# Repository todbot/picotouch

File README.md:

# picotouch

Tiny capsense touch USB MIDI keyboard from a Raspberry Pi Pico

If you're looking for the synthesizer version,
that's at [github.com/todbot/picotouch_synth](https://github.com/todbot/picotouch_synth)

## Demos

https://user-images.githubusercontent.com/274093/216477797-90a1e4ca-b68f-4eb2-be46-de1d6d81551e.mp4

Also see videos in this Twitter thread : https://twitter.com/todbot/status/1382469033061093377

And check out [picotouch videos on my Youtube channel](https://www.youtube.com/@todbot/search?query=picotouch)

## Materials needed

If you [buy a black 'picotouch SMD' board from my Tindie store](https://www.tindie.com/products/todbot/picotouch-capsense-midi-keyboard-for-raspi-pico/), the <b>resistors are soldered</b> for you, so you only need to
[solder the Pico](https://www.youtube.com/watch?v=dW9LiOq3Dso).

If you're building one by hand, you will need:
- 1 - picotouch PCB ([order from OSHpark](https://oshpark.com/shared_projects/5MnI1jPf))
- 1 - Raspberry Pi Pico  **(NOTE: Not the Pico2, since its RP2350 chip has a hardware error)**
- 23 - 1M ohm 0805 SMD resistors  ([Digikey cart with this & Pico](https://www.digikey.com/short/w381rn4w))

## How to solder the Pico

It's not too bad!  A pretty easy first-time SMD soldering project.  Here's
[how to solder the Pico down](https://www.youtube.com/watch?v=dW9LiOq3Dso).
The technique is: line up the Pico solder one corner, solder the other, then finish all the rest.
In the video you see I don't get it aligned perfectly straight (hard to see around the camera), but it still works great!  ([Youtube version of the below video](https://www.youtube.com/watch?v=dW9LiOq3Dso))

https://user-images.githubusercontent.com/274093/217670870-b04d55ed-e37d-4be2-bea7-4985d2b3f8c4.mp4

## Firmware Installation

* Install CircuitPython
  - Hold down BOOT button while plugging in Pico to get RPI-RP2 drive
  - Download CircuitPython UF2 from https://circuitpython.org/board/raspberry_pi_pico/
  - Drag UF2 to RPI-RP2 drive. CircuitPython is now installed!

* Install CircuitPython libraries onto Pico
  - If you have Python on your computer you can do:
    ```
    pip3 install circup
    circup install adafruit_midi adafruit_debouncer adafruit_ticks
    ```
  - Otherwise, download the CircuitPython Libraries Bundle at https://circuitpython.org/libraries
    and copy over the `adafruit_midi`, `adafruit_debouncer`, & `adafruit_ticks` libraries
    to the `CIRCUITPY/lib` folder on the Pico.

* Install picotouch `code.py`
  - Via commandline:
    ```
    cp picotouch/circuitpython/picotouch/code.py /Volumes/CIRCUITPY/code.py
    ```
  - Or you can drag-n-drop using your computer's GUI
  - Note: this will delete the previous `code.py` on your Pico.
      Normally this is fine, but if it's not, be sure to save it if you want to keep it!

## Going further

There's other things you can do with the picotouch board.

- Use it as a MIDI slider bank

    Install
   [`picotouch_midislider/code.py`](https://github.com/todbot/picotouch/blob/main/circuitpython/picotouch_midislider/code.py) instead of the regular picotouch code.py.

   - youtube demo: [midislider demo video](https://youtu.be/1Psw3PLqYS8)

- Use it as a HID keyboard macropad

   - example code: [`picotouch_macropad/code.py`](https://github.com/todbot/picotouch/blob/main/circuitpython/picotouch_macropad/code.py)

   It's early days, but it's a start at that idea

## Press

- https://www.hackster.io/news/tod-kurt-s-ultra-slim-picotouch-is-a-button-free-23-key-raspberry-pi-pico-powered-midi-keyboard-700a3ce2227b (26 Feb 2023)
- https://www.raspberrypi.com/news/picotouch-synthesiser-magpimonday/ (22 Nov 2023)

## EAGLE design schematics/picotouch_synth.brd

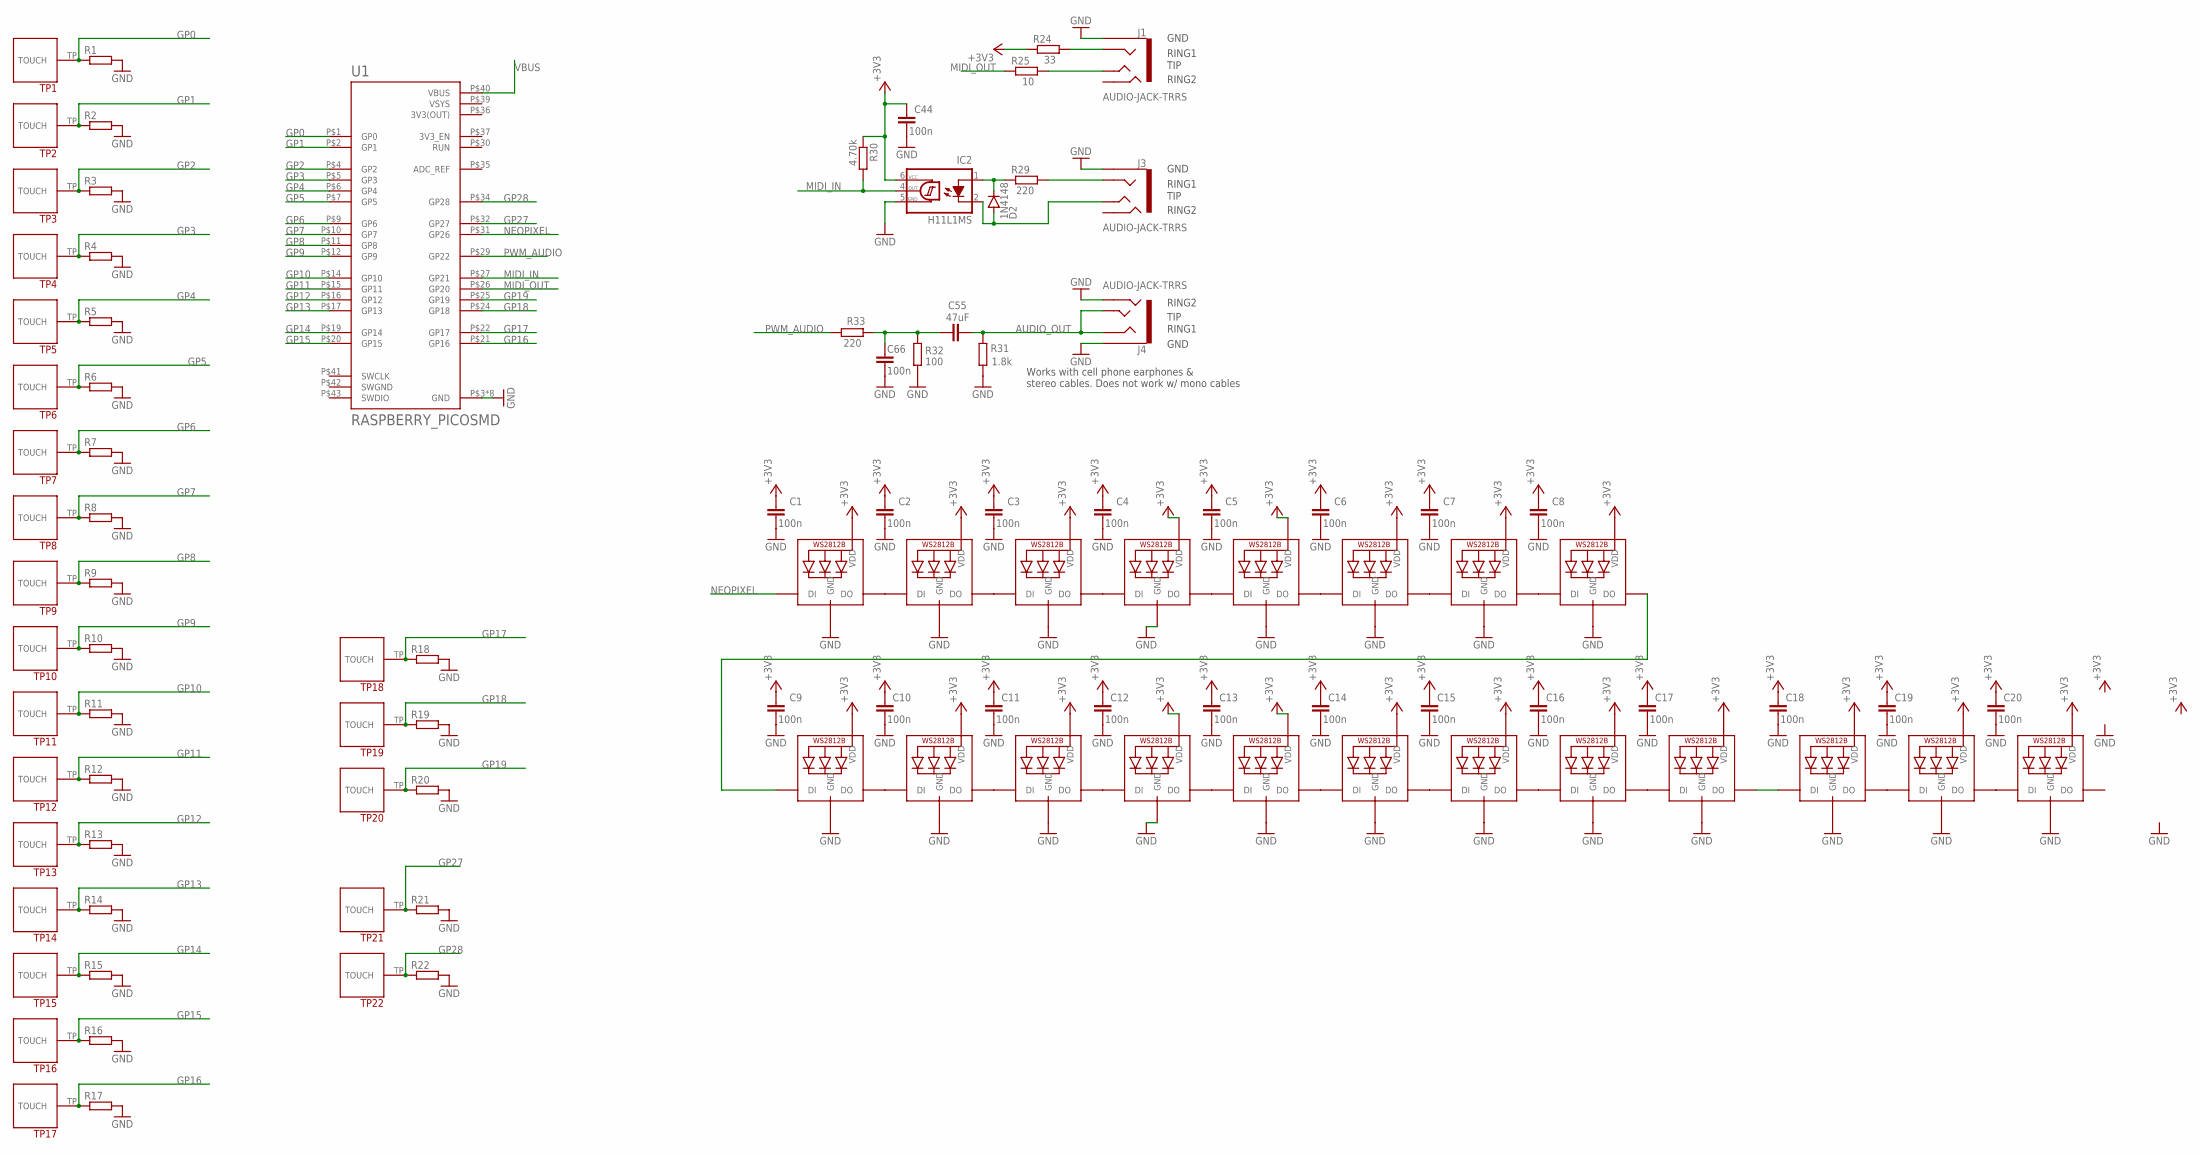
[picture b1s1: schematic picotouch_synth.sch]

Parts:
C1, C2, C3, C4, C5, C6, C7, C8, C9, C10, C11, C12, C13, C14, C15, C16, C17, C18, C19, C20, C44, C66: 100n; C0603
C55: 47uF; C0603
D2: 1N4148; SOD123
IC2: H11L1MS; DIL6-SMD; MPN2 H11L1S; LCSC C78589
J1, J3: AUDIO-JACK-TRRS; PJ-320D_SPARKFUN
J4: AUDIO-JACK-TRRS; PJ-320D_SPARKFUN; LCSC C431535
LED1, LED2, LED3, LED4, LED5, LED6, LED7, LED8, LED9, LED10, LED11, LED12, LED13, LED14, LED15, LED16, LED17, LED18, LED19, LED20: WS2812B3535; LED3535
R1, R2, R3, R4, R5, R6, R7, R8, R9, R10, R11, R12, R13, R14, R15, R16, R17: R-EU_R0805; R0805
R18, R19, R20, R21, R22: R-EU_R0603; R0603
R24: 33; R0603
R25: 10; R0603
R29, R33: 220; R0603
R30: 4.70k; R0603
R31: 1.8k; R0603
R32: 100; R0603
TP1, TP2, TP3, TP4, TP5, TP6, TP7, TP8, TP9, TP10, TP11, TP12, TP13, TP14, TP15, TP16, TP17: TOUCHPADA
TP18, TP19, TP20, TP21, TP22: TOUCHPADB
U1: RASPBERRY_PICOSMD; PICO-PKG-SMD

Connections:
3V3(OUT): U1.P$36 (3V3(OUT))
+3V3: C1.1, C2.1, C3.1, C4.1, C5.1, C6.1, C7.1, C8.1, C9.1, C10.1, C11.1, C12.1, C13.1, C14.1, C15.1, C16.1, C17.1, C18.1, C19.1, C20.1, C44.1, IC2.6 (VCC), LED1.2 (VDD), LED2.2 (VDD), LED3.2 (VDD), LED4.2 (VDD), LED5.2 (VDD), LED6.2 (VDD), LED7.2 (VDD), LED8.2 (VDD), LED9.2 (VDD), LED10.2 (VDD), LED11.2 (VDD), LED12.2 (VDD), LED13.2 (VDD), LED14.2 (VDD), LED15.2 (VDD), LED16.2 (VDD), LED17.2 (VDD), LED18.2 (VDD), LED19.2 (VDD), LED20.2 (VDD), R24.1, R30.1
AUDIO_OUT: C55.2, J4.RING1, J4.TIP, R31.1
GND: C1.2, C2.2, C3.2, C4.2, C5.2, C6.2, C7.2, C8.2, C9.2, C10.2, C11.2, C12.2, C13.2, C14.2, C15.2, C16.2, C17.2, C18.2, C19.2, C20.2, C44.2, C66.2, IC2.5 (GND), J1.EARTH, J3.EARTH, J4.EARTH, J4.RING2, LED1.4 (GND), LED2.4 (GND), LED3.4 (GND), LED4.4 (GND), LED5.4 (GND), LED6.4 (GND), LED7.4 (GND), LED8.4 (GND), LED9.4 (GND), LED10.4 (GND), LED11.4 (GND), LED12.4 (GND), LED13.4 (GND), LED14.4 (GND), LED15.4 (GND), LED16.4 (GND), LED17.4 (GND), LED18.4 (GND), LED19.4 (GND), LED20.4 (GND), R1.2, R2.2, R3.2, R4.2, R5.2, R6.2, R7.2, R8.2, R9.2, R10.2, R11.2, R12.2, R13.2, R14.2, R15.2, R16.2, R17.2, R18.2, R19.2, R20.2, R21.2, R22.2, R31.2, R32.1, U1.P$3 (GND), U1.P$8 (GND), U1.P$13 (GND), U1.P$18 (GND), U1.P$23 (GND), U1.P$28 (GND), U1.P$33 (GND), U1.P$38 (GND)
GP0: R1.1, TP1.TP, U1.P$1 (GP0)
GP1: R2.1, TP2.TP, U1.P$2 (GP1)
GP2: R3.1, TP3.TP, U1.P$4 (GP2)
GP3: R4.1, TP4.TP, U1.P$5 (GP3)
GP4: R5.1, TP5.TP, U1.P$6 (GP4)
GP5: R6.1, TP6.TP, U1.P$7 (GP5)
GP6: R7.1, TP7.TP, U1.P$9 (GP6)
GP7: R8.1, TP8.TP, U1.P$10 (GP7)
GP8: R9.1, TP9.TP, U1.P$11 (GP8)
GP9: R10.1, TP10.TP, U1.P$12 (GP9)
GP10: R11.1, TP11.TP, U1.P$14 (GP10)
GP11: R12.1, TP12.TP, U1.P$15 (GP11)
GP12: R13.1, TP13.TP, U1.P$16 (GP12)
GP13: R14.1, TP14.TP, U1.P$17 (GP13)
GP14: R15.1, TP15.TP, U1.P$19 (GP14)
GP15: R16.1, TP16.TP, U1.P$20 (GP15)
GP16: R17.1, TP17.TP, U1.P$21 (GP16)
GP17: R18.1, TP18.TP, U1.P$22 (GP17)
GP18: R19.1, TP19.TP, U1.P$24 (GP18)
GP19: R20.1, TP20.TP, U1.P$25 (GP19)
GP27: R21.1, TP21.TP, U1.P$32 (GP27)
GP28: R22.1, TP22.TP, U1.P$34 (GP28)
MIDI_IN: IC2.4 (OUT), R30.2, U1.P$27 (GP21)
MIDI_OUT: R25.1, U1.P$26 (GP20)
unnamed: D2.C, IC2.1 (A), R29.1
unnamed: J1.TIP, R25.2
unnamed: D2.A, IC2.2 (C), J3.TIP
unnamed: J3.RING1, R29.2
unnamed: C55.1, C66.1, R32.2, R33.1
unnamed: J1.RING1, R24.2
unnamed: LED1.3 (DO), LED2.1 (DI)
unnamed: LED4.3 (DO), LED5.1 (DI)
unnamed: LED5.3 (DO), LED6.1 (DI)
unnamed: LED6.3 (DO), LED7.1 (DI)
unnamed: LED7.3 (DO), LED8.1 (DI)
unnamed: LED2.3 (DO), LED3.1 (DI)
unnamed: LED3.3 (DO), LED4.1 (DI)
unnamed: LED9.3 (DO), LED10.1 (DI)
unnamed: LED12.3 (DO), LED13.1 (DI)
unnamed: LED13.3 (DO), LED14.1 (DI)
unnamed: LED14.3 (DO), LED15.1 (DI)
unnamed: LED15.3 (DO), LED16.1 (DI)
unnamed: LED10.3 (DO), LED11.1 (DI)
unnamed: LED11.3 (DO), LED12.1 (DI)
unnamed: LED8.3 (DO), LED9.1 (DI)
unnamed: LED16.3 (DO), LED17.1 (DI)
unnamed: LED18.3 (DO), LED19.1 (DI)
unnamed: LED19.3 (DO), LED20.1 (DI)
unnamed: LED17.3 (DO), LED18.1 (DI)
NEOPIXEL: LED1.1 (DI), U1.P$31 (GP26)
PWM_AUDIO: R33.2, U1.P$29 (GP22)
SWGND: U1.P$42 (SWGND)
VBUS: U1.P$40 (VBUS)
VSYS: U1.P$39 (VSYS)

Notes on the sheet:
RING2
RING1
GND
TIP
Works with cell phone earphones & stereo cables. Does not work w/ mono cables

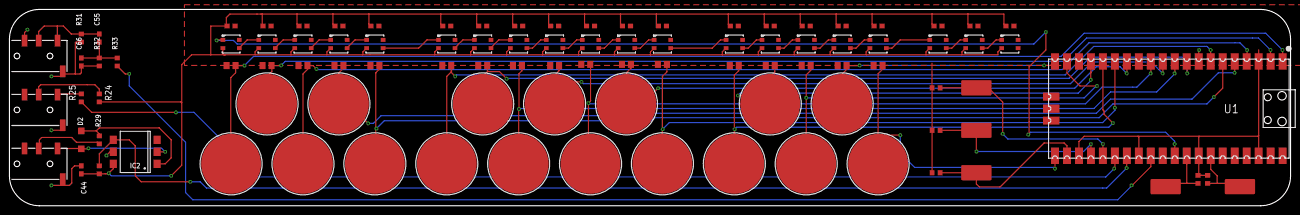
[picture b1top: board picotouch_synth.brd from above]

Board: 2 copper layers, 271.6 x 41.6 mm, 100 parts (0 on the bottom side), 54 nets.

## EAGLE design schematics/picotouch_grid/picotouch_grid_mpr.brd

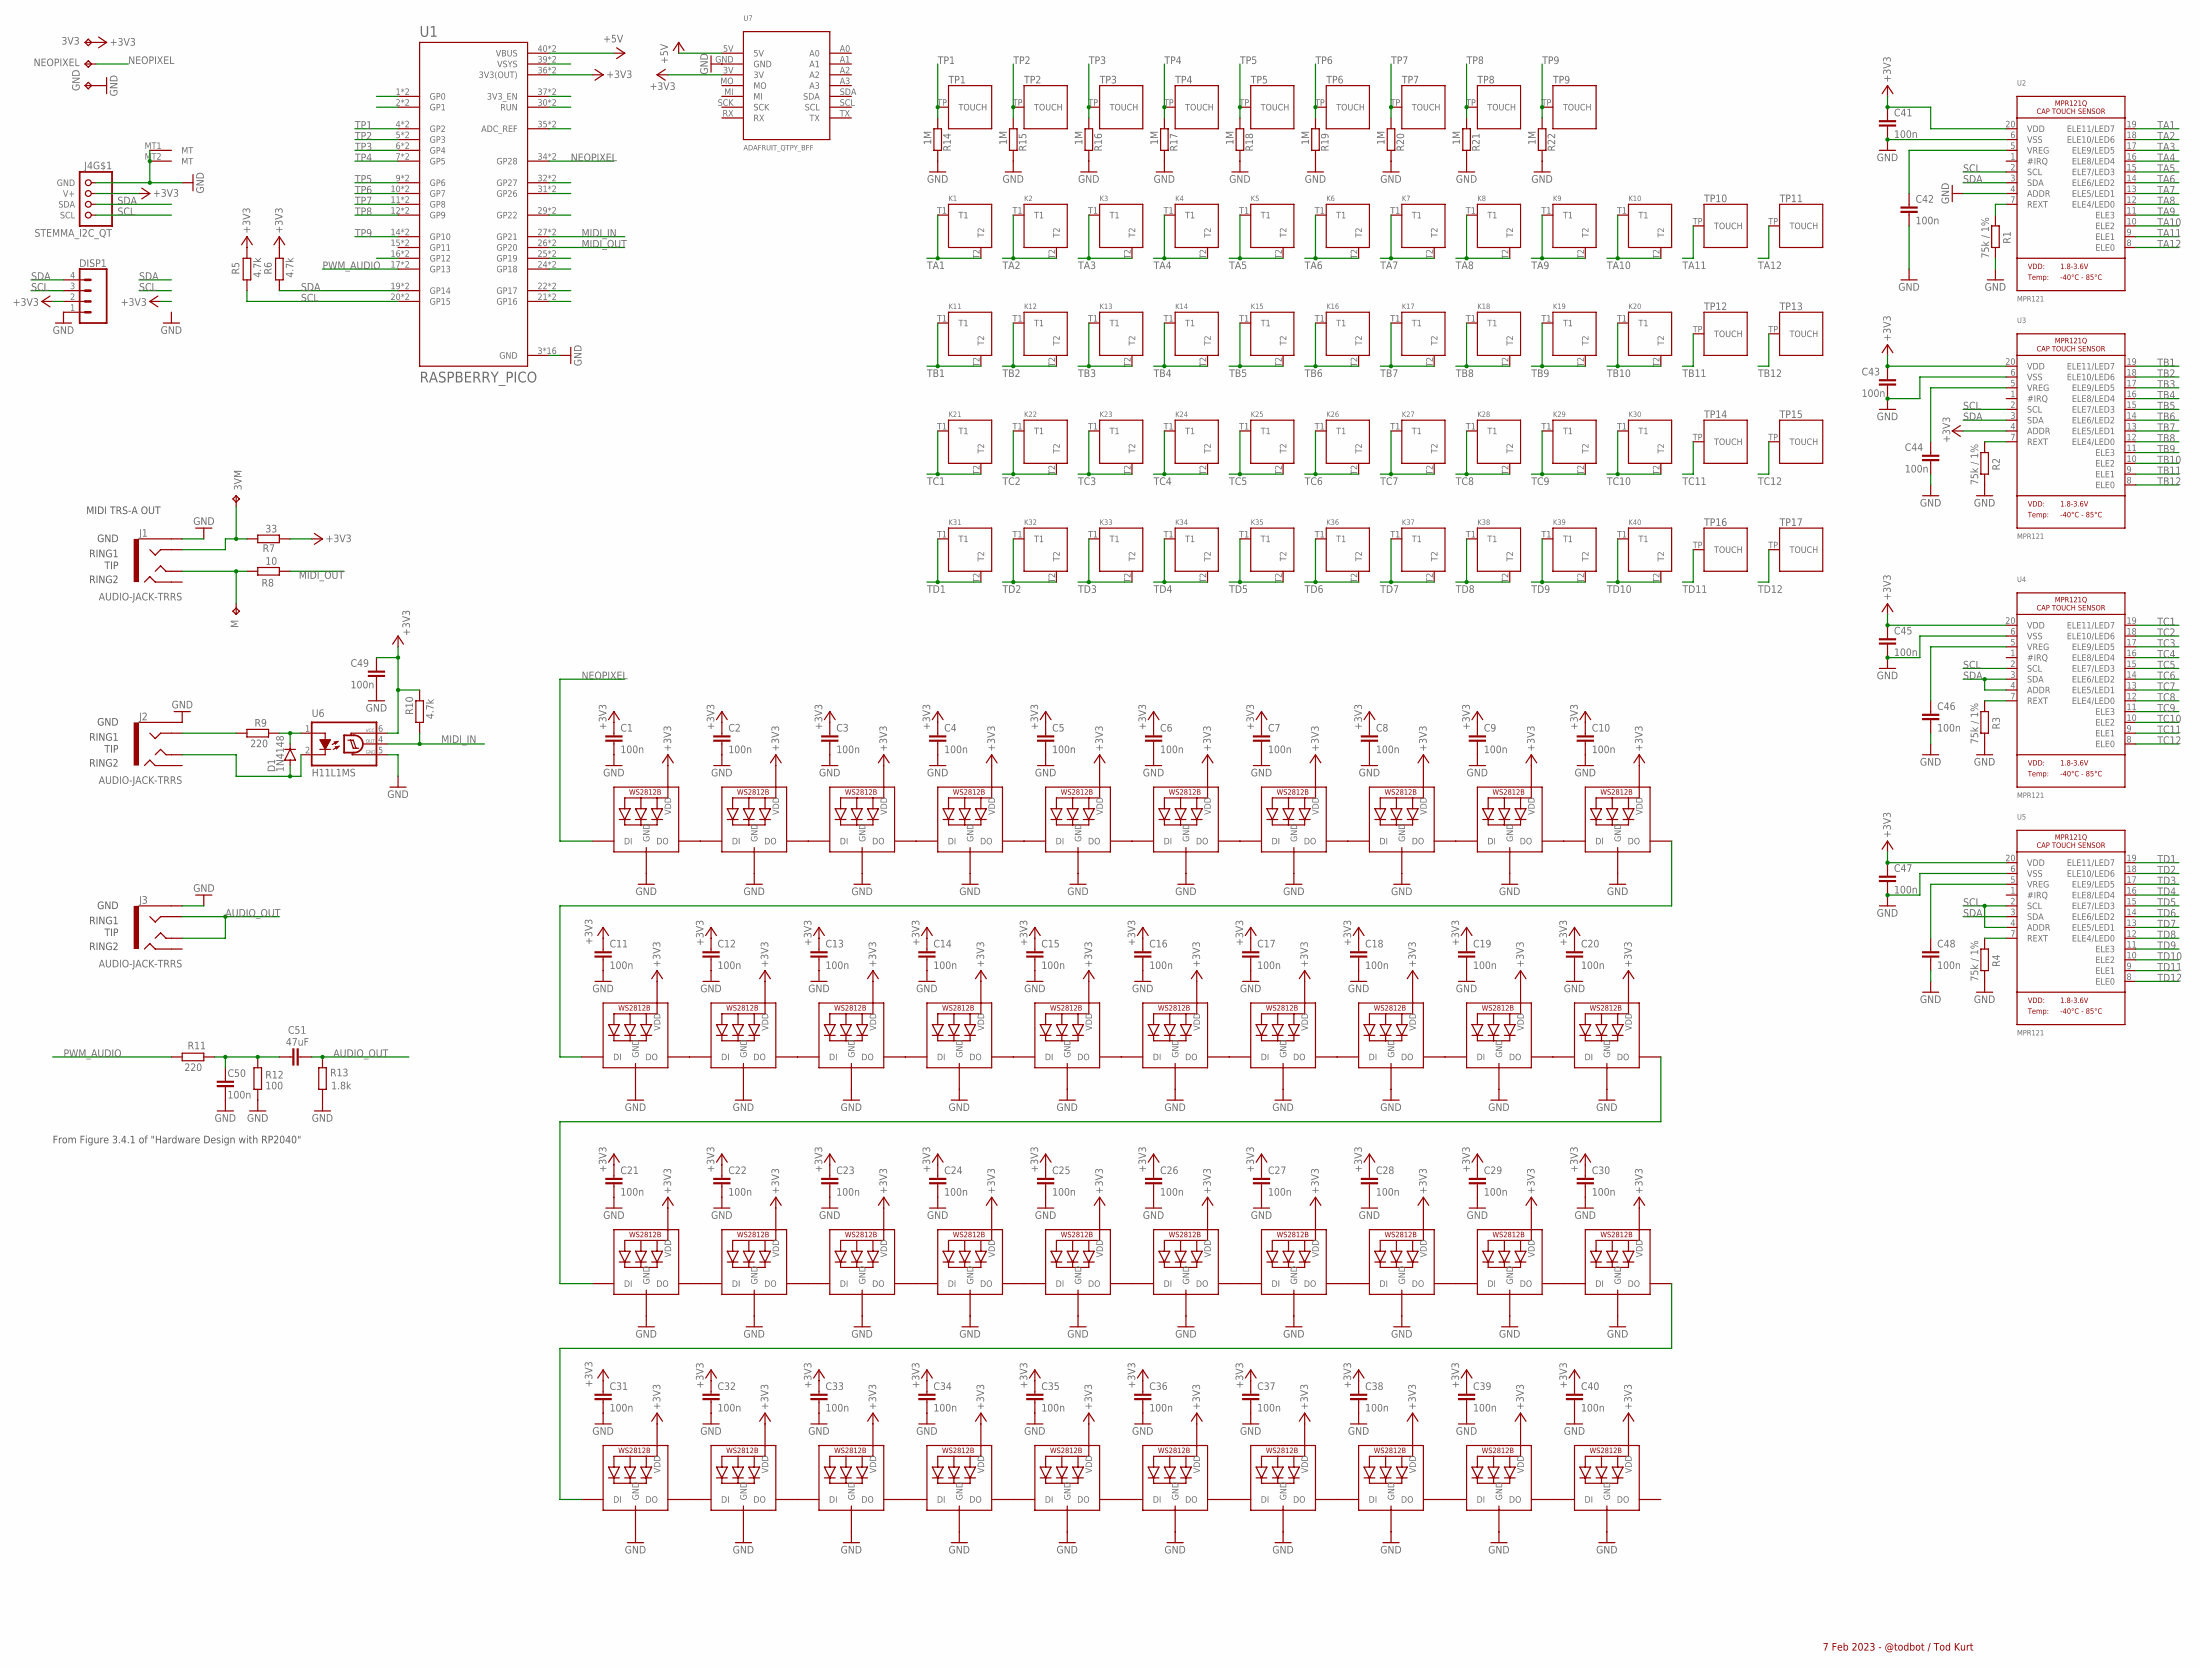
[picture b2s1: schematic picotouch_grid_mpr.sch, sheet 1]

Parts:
3V3, 3VM: TPTP15R; TP15R
C1, C2, C3, C4, C5, C6, C7, C8, C9, C10, C11, C12, C13, C14, C15, C16, C17, C18, C19, C20, C21, C22, C23, C24, C25, C26, C27, C28, C29, C30, C31, C32, C33, C34, C35, C36, C37, C38, C39, C40, C41, C42, C43, C44, C45, C46, C47, C48, C49, C50: 100n; C0603
C51: 47uF; C0805
D1: 1N4148; SOD123
DISP1: CONN_04; 1X04
GND: TPTP15R; TP15R
J1, J3: AUDIO-JACK-TRRS; PJ-320D_SPARKFUN; LCSC C431535
J2: AUDIO-JACK-TRRS; PJ-320D_SPARKFUN
J4: STEMMA_I2C_QT; JST_SH4; MPN HC-1.0-4PWT; LCSC2 C160404
K1, K2, K3, K4, K5, K6, K7, K8, K9, K10, K11, K12, K13, K14, K15, K16, K17, K18, K19, K20, K21, K22, K23, K24, K25, K26, K27, K28, K29, K30, K31, K32, K33, K34, K35, K36, K37, K38, K39, K40: TOUCHKEYH; TOUCHPAD_KEY_0.5IN_LEDHOLE
LED1: MICROBUILDER_WS2812B_SK6812E; MICROBUILDER_NEO3535_REVERSE; LCSC C5149201
LED2, LED3, LED4, LED5, LED6, LED7, LED8, LED9, LED10, LED11, LED12, LED13, LED14, LED15, LED16, LED17, LED18, LED19, LED20, LED21, LED22, LED23, LED24, LED25, LED26, LED27, LED28, LED29, LED30, LED31, LED32, LED33, LED34, LED35, LED36, LED37, LED38, LED39, LED40: MICROBUILDER_WS2812B_SK6812E; MICROBUILDER_NEO3535_REVERSE
M: TPTP15R; TP15R
NEOPIXEL: TPTP15R; TP15R
R1, R2, R3, R4: 75k / 1%; R0603
R5, R6, R10: 4.7k; R0603
R7: 33; R0603
R8: 10; R0603
R9, R11: 220; R0603
R12: 100; R0603
R13: 1.8k; R0603
R14, R15, R16, R17, R18, R19, R20, R21, R22: 1M; R0603
TP1, TP2, TP3, TP4, TP5, TP6, TP7, TP8, TP9, TP10, TP11, TP12, TP13, TP14, TP15, TP16, TP17: TOUCHPADB
U1: RASPBERRY_PICO; PICO-PKG-DUALSMD
U2, U3, U4, U5: MPR121; QFN20_3MM_NOTHERMAL; LCSC C91322
U6: H11L1MS; DIL6-SMD; MPN2 H11L1S; LCSC C78589
U7: ADAFRUIT_QTPY_BFF; ADAFRUIT_QTPY_BFF_LIPO

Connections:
+3V3: 3V3.TP, C1.1, C2.1, C3.1, C4.1, C5.1, C6.1, C7.1, C8.1, C9.1, C10.1, C11.1, C12.1, C13.1, C14.1, C15.1, C16.1, C17.1, C18.1, C19.1, C20.1, C21.1, C22.1, C23.1, C24.1, C25.1, C26.1, C27.1, C28.1, C29.1, C30.1, C31.1, C32.1, C33.1, C34.1, C35.1, C36.1, C37.1, C38.1, C39.1, C40.1, C41.1, C43.1, C45.1, C47.1, C49.1, DISP1.2, J4.2 (V+), LED1.1-VDD (VDD), LED2.1-VDD (VDD), LED3.1-VDD (VDD), LED4.1-VDD (VDD), LED5.1-VDD (VDD), LED6.1-VDD (VDD), LED7.1-VDD (VDD), LED8.1-VDD (VDD), LED9.1-VDD (VDD), LED10.1-VDD (VDD), LED11.1-VDD (VDD), LED12.1-VDD (VDD), LED13.1-VDD (VDD), LED14.1-VDD (VDD), LED15.1-VDD (VDD), LED16.1-VDD (VDD), LED17.1-VDD (VDD), LED18.1-VDD (VDD), LED19.1-VDD (VDD), LED20.1-VDD (VDD), LED21.1-VDD (VDD), LED22.1-VDD (VDD), LED23.1-VDD (VDD), LED24.1-VDD (VDD), LED25.1-VDD (VDD), LED26.1-VDD (VDD), LED27.1-VDD (VDD), LED28.1-VDD (VDD), LED29.1-VDD (VDD), LED30.1-VDD (VDD), LED31.1-VDD (VDD), LED32.1-VDD (VDD), LED33.1-VDD (VDD), LED34.1-VDD (VDD), LED35.1-VDD (VDD), LED36.1-VDD (VDD), LED37.1-VDD (VDD), LED38.1-VDD (VDD), LED39.1-VDD (VDD), LED40.1-VDD (VDD), R5.1, R6.1, R7.2, R10.1, U1.36 (3V3(OUT)), U1.36' (3V3(OUT)), U2.20 (VDD), U3.4 (ADDR), U3.20 (VDD), U4.20 (VDD), U5.20 (VDD), U6.6 (VCC), U7.3V
+5V: U1.40 (VBUS), U1.40' (VBUS), U7.5V
AUDIO_OUT: C51.2, J3.RING1, J3.TIP, R13.1
GND: C1.2, C2.2, C3.2, C4.2, C5.2, C6.2, C7.2, C8.2, C9.2, C10.2, C11.2, C12.2, C13.2, C14.2, C15.2, C16.2, C17.2, C18.2, C19.2, C20.2, C21.2, C22.2, C23.2, C24.2, C25.2, C26.2, C27.2, C28.2, C29.2, C30.2, C31.2, C32.2, C33.2, C34.2, C35.2, C36.2, C37.2, C38.2, C39.2, C40.2, C41.2, C42.2, C43.2, C44.2, C45.2, C46.2, C47.2, C48.2, C49.2, C50.2, DISP1.1, GND.TP, J1.EARTH, J2.EARTH, J3.EARTH, J4.1 (GND), J4.MT1 (MT), J4.MT2 (MT), LED1.3-GND (GND), LED2.3-GND (GND), LED3.3-GND (GND), LED4.3-GND (GND), LED5.3-GND (GND), LED6.3-GND (GND), LED7.3-GND (GND), LED8.3-GND (GND), LED9.3-GND (GND), LED10.3-GND (GND), LED11.3-GND (GND), LED12.3-GND (GND), LED13.3-GND (GND), LED14.3-GND (GND), LED15.3-GND (GND), LED16.3-GND (GND), LED17.3-GND (GND), LED18.3-GND (GND), LED19.3-GND (GND), LED20.3-GND (GND), LED21.3-GND (GND), LED22.3-GND (GND), LED23.3-GND (GND), LED24.3-GND (GND), LED25.3-GND (GND), LED26.3-GND (GND), LED27.3-GND (GND), LED28.3-GND (GND), LED29.3-GND (GND), LED30.3-GND (GND), LED31.3-GND (GND), LED32.3-GND (GND), LED33.3-GND (GND), LED34.3-GND (GND), LED35.3-GND (GND), LED36.3-GND (GND), LED37.3-GND (GND), LED38.3-GND (GND), LED39.3-GND (GND), LED40.3-GND (GND), R1.1, R2.1, R3.1, R4.1, R12.1, R13.2, R14.1, R15.1, R16.1, R17.1, R18.1, R19.1, R20.1, R21.1, R22.1, U1.3 (GND), U1.3' (GND), U1.8 (GND), U1.8' (GND), U1.13 (GND), U1.13' (GND), U1.18 (GND), U1.18' (GND), U1.23 (GND), U1.23' (GND), U1.28 (GND), U1.28' (GND), U1.33 (GND), U1.33' (GND), U1.38 (GND), U1.38' (GND), U2.4 (ADDR), U2.6 (VSS), U3.6 (VSS), U4.6 (VSS), U5.6 (VSS), U6.5 (GND), U7.GND
MIDI_IN: R10.2, U1.27 (GP21), U1.27' (GP21), U6.4 (OUT)
MIDI_OUT: R8.2, U1.26 (GP20), U1.26' (GP20)
unnamed: LED1.2-DOUT (DO), LED2.4-DIN (DI)
unnamed: LED2.2-DOUT (DO), LED3.4-DIN (DI)
unnamed: LED4.2-DOUT (DO), LED5.4-DIN (DI)
unnamed: LED5.2-DOUT (DO), LED6.4-DIN (DI)
unnamed: LED3.2-DOUT (DO), LED4.4-DIN (DI)
unnamed: LED7.2-DOUT (DO), LED8.4-DIN (DI)
unnamed: LED8.2-DOUT (DO), LED9.4-DIN (DI)
unnamed: J1.TIP, M.TP, R8.1
unnamed: LED11.2-DOUT (DO), LED12.4-DIN (DI)
unnamed: LED9.2-DOUT (DO), LED10.4-DIN (DI)
unnamed: LED6.2-DOUT (DO), LED7.4-DIN (DI)
unnamed: LED14.2-DOUT (DO), LED15.4-DIN (DI)
unnamed: LED15.2-DOUT (DO), LED16.4-DIN (DI)
unnamed: LED13.2-DOUT (DO), LED14.4-DIN (DI)
unnamed: LED17.2-DOUT (DO), LED18.4-DIN (DI)
unnamed: LED18.2-DOUT (DO), LED19.4-DIN (DI)
unnamed: LED19.2-DOUT (DO), LED20.4-DIN (DI)
unnamed: LED16.2-DOUT (DO), LED17.4-DIN (DI)
unnamed: LED12.2-DOUT (DO), LED13.4-DIN (DI)
unnamed: LED21.2-DOUT (DO), LED22.4-DIN (DI)
unnamed: LED22.2-DOUT (DO), LED23.4-DIN (DI)
unnamed: LED24.2-DOUT (DO), LED25.4-DIN (DI)
unnamed: LED25.2-DOUT (DO), LED26.4-DIN (DI)
unnamed: LED23.2-DOUT (DO), LED24.4-DIN (DI)
unnamed: LED27.2-DOUT (DO), LED28.4-DIN (DI)
unnamed: LED28.2-DOUT (DO), LED29.4-DIN (DI)
unnamed: LED31.2-DOUT (DO), LED32.4-DIN (DI)
unnamed: LED29.2-DOUT (DO), LED30.4-DIN (DI)
unnamed: LED26.2-DOUT (DO), LED27.4-DIN (DI)
unnamed: LED34.2-DOUT (DO), LED35.4-DIN (DI)
unnamed: LED35.2-DOUT (DO), LED36.4-DIN (DI)
unnamed: LED33.2-DOUT (DO), LED34.4-DIN (DI)
unnamed: LED37.2-DOUT (DO), LED38.4-DIN (DI)
unnamed: LED38.2-DOUT (DO), LED39.4-DIN (DI)
unnamed: LED39.2-DOUT (DO), LED40.4-DIN (DI)
unnamed: LED36.2-DOUT (DO), LED37.4-DIN (DI)
unnamed: LED32.2-DOUT (DO), LED33.4-DIN (DI)
unnamed: 3VM.TP, J1.RING1, R7.1
unnamed: U1.21 (GP16), U1.21' (GP16)
unnamed: U1.22 (GP17), U1.22' (GP17)
unnamed: U1.24 (GP18), U1.24' (GP18)
unnamed: U1.25 (GP19), U1.25' (GP19)
unnamed: R2.2, U3.7 (REXT)
unnamed: C44.1, U3.5 (VREG)
unnamed: U1.32 (GP27), U1.32' (GP27)
unnamed: D1.C, R9.1, U6.1 (A)
unnamed: D1.A, J2.TIP, U6.2 (C)
unnamed: J2.RING1, R9.2
unnamed: R4.2, U5.7 (REXT)
unnamed: C48.1, U5.5 (VREG)
unnamed: U1.31 (GP26), U1.31' (GP26)
unnamed: U1.29 (GP22), U1.29' (GP22)
unnamed: U1.35 (ADC_REF), U1.35' (ADC_REF)
unnamed: U1.30 (RUN), U1.30' (RUN)
unnamed: C50.1, C51.1, R11.1, R12.2
unnamed: U1.37 (3V3_EN), U1.37' (3V3_EN)
unnamed: U1.2 (GP1), U1.2' (GP1)
unnamed: R3.2, U4.7 (REXT)
unnamed: C46.1, U4.5 (VREG)
unnamed: U1.1 (GP0), U1.1' (GP0)
unnamed: U1.39 (VSYS), U1.39' (VSYS)
unnamed: U1.16 (GP12), U1.16' (GP12)
unnamed: C42.1, U2.5 (VREG)
unnamed: R1.2, U2.7 (REXT)
NEOPIXEL: LED1.4-DIN (DI), NEOPIXEL.TP, U1.34 (GP28), U1.34' (GP28)
NEOPIXEL0: LED10.2-DOUT (DO), LED11.4-DIN (DI)
NEOPIXEL1: LED20.2-DOUT (DO), LED21.4-DIN (DI)
NEOPIXEL2: LED30.2-DOUT (DO), LED31.4-DIN (DI)
PWM_AUDIO: R11.2, U1.17 (GP13), U1.17' (GP13)
SCL: DISP1.3, J4.4 (SCL), R5.2, U1.20 (GP15), U1.20' (GP15), U2.2 (SCL), U3.2 (SCL), U4.2 (SCL), U5.2 (SCL), U5.4 (ADDR)
SDA: DISP1.4, J4.3 (SDA), R6.2, U1.19 (GP14), U1.19' (GP14), U2.3 (SDA), U3.3 (SDA), U4.3 (SDA), U4.4 (ADDR), U5.3 (SDA)
TA1: K1.T1, K1.T2, U2.19 (ELE11/LED7)
TA2: K2.T1, K2.T2, U2.18 (ELE10/LED6)
TA3: K3.T1, K3.T2, U2.17 (ELE9/LED5)
TA4: K4.T1, K4.T2, U2.16 (ELE8/LED4)
TA5: K5.T1, K5.T2, U2.15 (ELE7/LED3)
TA6: K6.T1, K6.T2, U2.14 (ELE6/LED2)
TA7: K7.T1, K7.T2, U2.13 (ELE5/LED1)
TA8: K8.T1, K8.T2, U2.12 (ELE4/LED0)
TA9: K9.T1, K9.T2, U2.11 (ELE3)
TA10: K10.T1, K10.T2, U2.10 (ELE2)
TA11: TP10.TP, U2.9 (ELE1)
TA12: TP11.TP, U2.8 (ELE0)
TB1: K11.T1, K11.T2, U3.19 (ELE11/LED7)
TB2: K12.T1, K12.T2, U3.18 (ELE10/LED6)
TB3: K13.T1, K13.T2, U3.17 (ELE9/LED5)
TB4: K14.T1, K14.T2, U3.16 (ELE8/LED4)
TB5: K15.T1, K15.T2, U3.15 (ELE7/LED3)
TB6: K16.T1, K16.T2, U3.14 (ELE6/LED2)
TB7: K17.T1, K17.T2, U3.13 (ELE5/LED1)
TB8: K18.T1, K18.T2, U3.12 (ELE4/LED0)
TB9: K19.T1, K19.T2, U3.11 (ELE3)
TB10: K20.T1, K20.T2, U3.10 (ELE2)
TB11: TP12.TP, U3.9 (ELE1)
TB12: TP13.TP, U3.8 (ELE0)
TC1: K21.T1, K21.T2, U4.19 (ELE11/LED7)
TC2: K22.T1, K22.T2, U4.18 (ELE10/LED6)
TC3: K23.T1, K23.T2, U4.17 (ELE9/LED5)
TC4: K24.T1, K24.T2, U4.16 (ELE8/LED4)
TC5: K25.T1, K25.T2, U4.15 (ELE7/LED3)
TC6: K26.T1, K26.T2, U4.14 (ELE6/LED2)
TC7: K27.T1, K27.T2, U4.13 (ELE5/LED1)
TC8: K28.T1, K28.T2, U4.12 (ELE4/LED0)
TC9: K29.T1, K29.T2, U4.11 (ELE3)
TC10: K30.T1, K30.T2, U4.10 (ELE2)
TC11: TP14.TP, U4.9 (ELE1)
TC12: TP15.TP, U4.8 (ELE0)
TD1: K31.T1, K31.T2, U5.19 (ELE11/LED7)
TD2: K32.T1, K32.T2, U5.18 (ELE10/LED6)
TD3: K33.T1, K33.T2, U5.17 (ELE9/LED5)
TD4: K34.T1, K34.T2, U5.16 (ELE8/LED4)
TD5: K35.T1, K35.T2, U5.15 (ELE7/LED3)
TD6: K36.T1, K36.T2, U5.14 (ELE6/LED2)
TD7: K37.T1, K37.T2, U5.13 (ELE5/LED1)
TD8: K38.T1, K38.T2, U5.12 (ELE4/LED0)
TD9: K39.T1, K39.T2, U5.11 (ELE3)
TD10: K40.T1, K40.T2, U5.10 (ELE2)
TD11: TP16.TP, U5.9 (ELE1)
TD12: TP17.TP, U5.8 (ELE0)
TP1: R14.2, TP1.TP, U1.4 (GP2), U1.4' (GP2)
TP2: R15.2, TP2.TP, U1.5 (GP3), U1.5' (GP3)
TP3: R16.2, TP3.TP, U1.6 (GP4), U1.6' (GP4)
TP4: R17.2, TP4.TP, U1.7 (GP5), U1.7' (GP5)
TP5: R18.2, TP5.TP, U1.9 (GP6), U1.9' (GP6)
TP6: R19.2, TP6.TP, U1.10 (GP7), U1.10' (GP7)
TP7: R20.2, TP7.TP, U1.11 (GP8), U1.11' (GP8)
TP8: R21.2, TP8.TP, U1.12 (GP9), U1.12' (GP9)
TP9: R22.2, TP9.TP, U1.14 (GP10), U1.14' (GP10)

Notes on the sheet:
MIDI TRS-A OUT
RING2
RING1
GND
TIP
7 Feb 2023 - @todbot / Tod Kurt
From Figure 3.4.1 of "Hardware Design with RP2040"

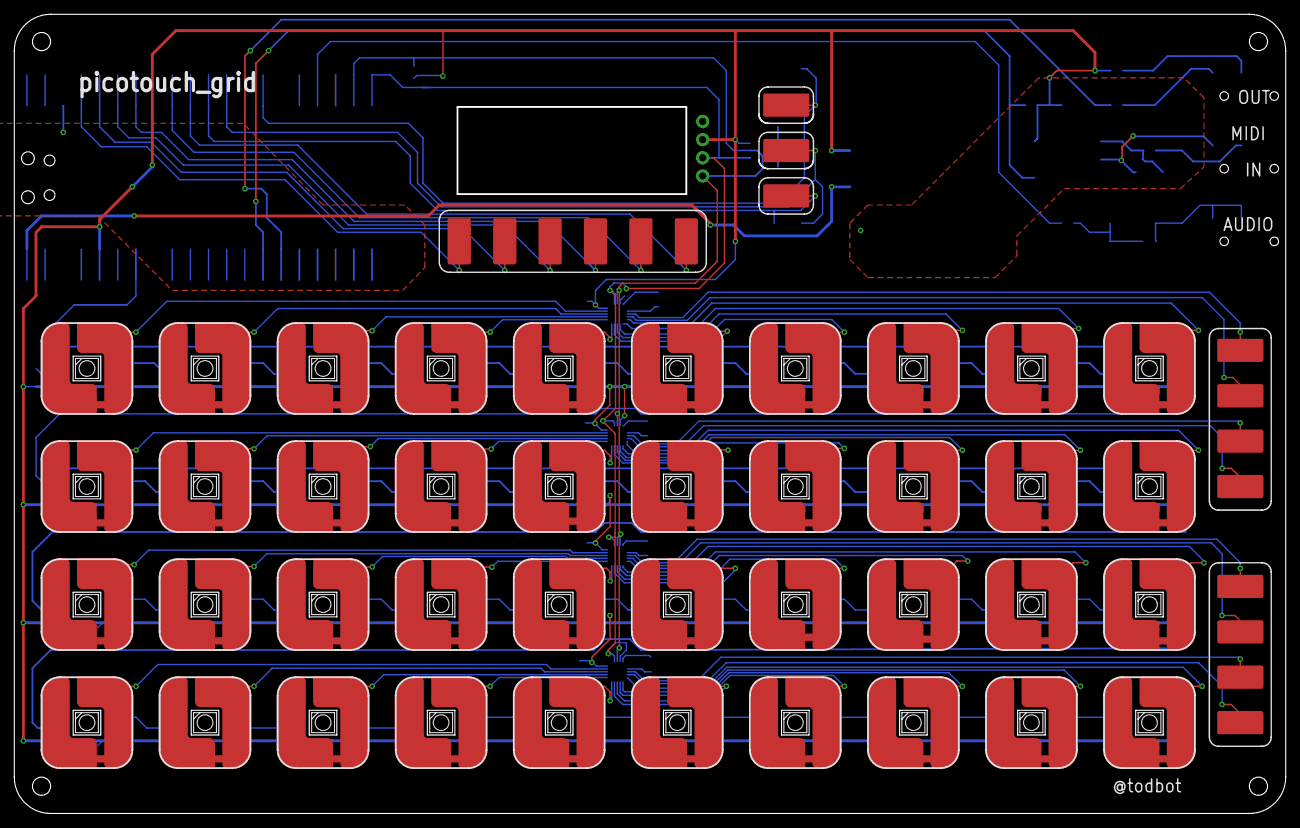
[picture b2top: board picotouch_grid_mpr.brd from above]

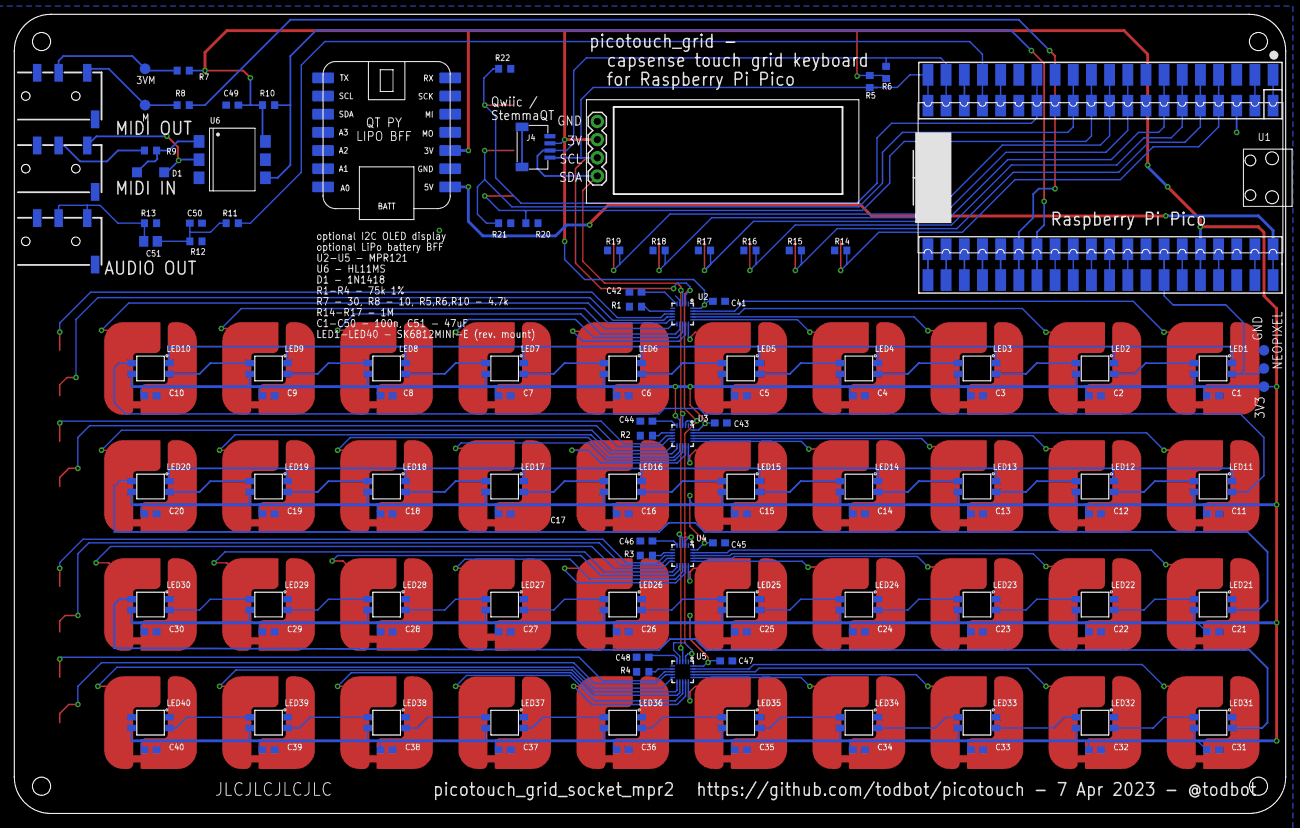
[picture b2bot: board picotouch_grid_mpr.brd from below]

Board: 2 copper layers, 177.8 x 111.8 mm, 188 parts (91 on the bottom side), 134 nets.

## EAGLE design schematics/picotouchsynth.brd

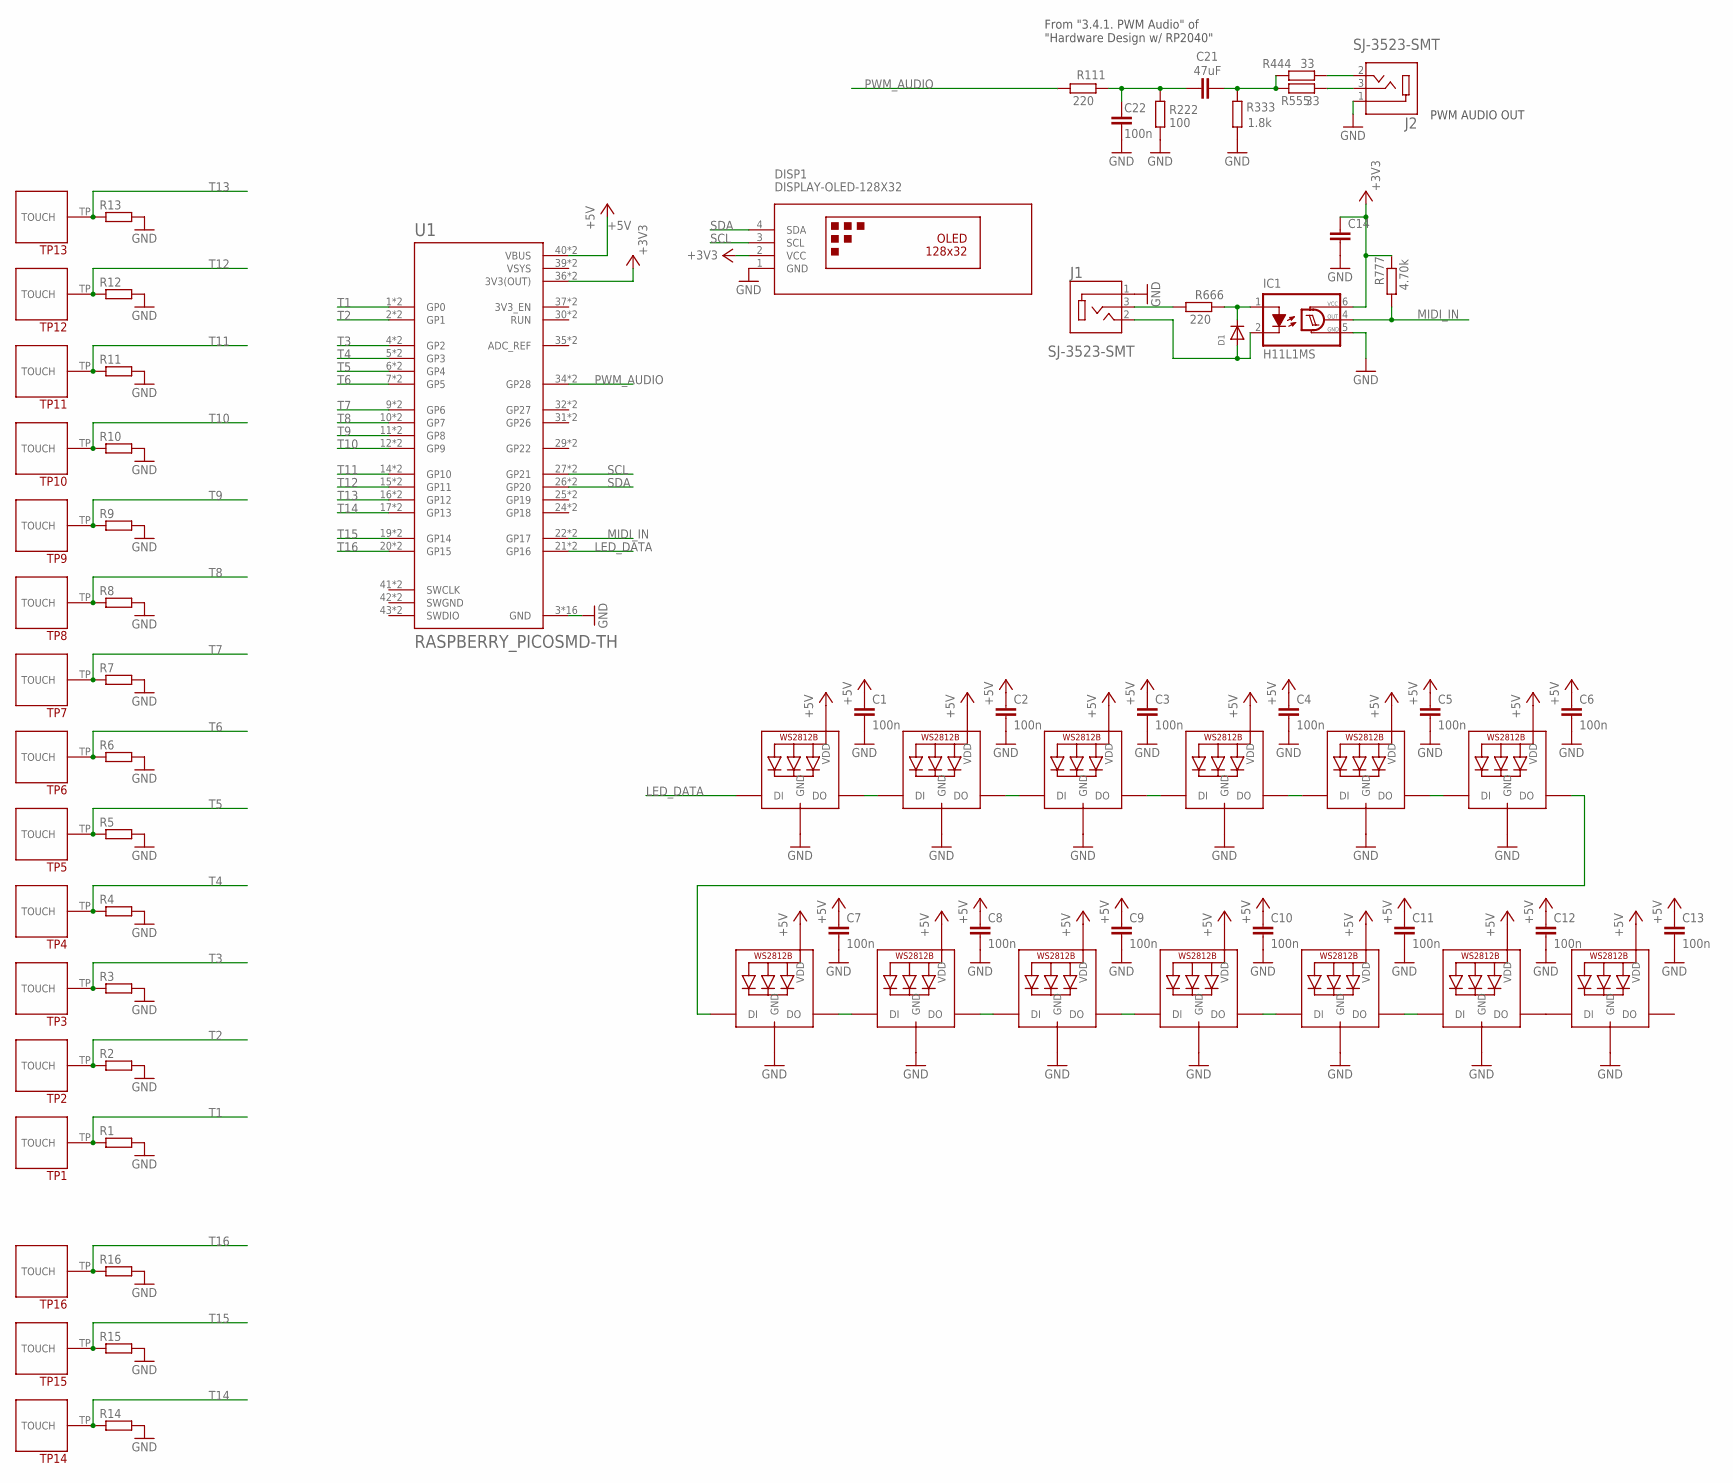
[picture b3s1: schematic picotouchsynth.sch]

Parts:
C1, C2, C3, C4, C5, C6, C7, C8, C9, C10, C11, C12, C13, C22: 100n; C0805
C14: C-EUC0805; C0805
C21: 47uF; C0805
D1: DIODESOD-523; SOD-523
DISP1: DISPLAY-OLED-128X32
IC1: H11L1MS; DIL6-SMD
J1, J2: SJ-3523-SMT; CUI_SJ-3523-SMT
LED1, LED2, LED3, LED4, LED5, LED6, LED7, LED8, LED9, LED10, LED11, LED12, LED13: MICROBUILDER_WS2812B_SK6812E; MICROBUILDER_NEO3535_REVERSE
R1, R2, R3, R4, R5, R6, R7, R8, R9, R10, R11, R12, R13, R14, R15, R16: R-EU_R0805; R0805
R111, R666: 220; R0805
R222: 100; R0805
R333: 1.8k; R0805
R444, R555: 33; R0805
R777: 4.70k; R0805
TP1, TP2, TP3, TP4, TP5, TP6, TP7, TP8, TP9, TP10, TP11, TP12, TP13: TOUCHPADA
TP14, TP15, TP16: TOUCHPADB
U1: RASPBERRY_PICOSMD-TH; PICO-PKG

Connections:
+3V3: C14.1, DISP1.2 (VCC), IC1.6 (VCC), R777.1, U1.36 (3V3(OUT)), U1.P$36 (3V3(OUT))
+5V: C1.1, C2.1, C3.1, C4.1, C5.1, C6.1, C7.1, C8.1, C9.1, C10.1, C11.1, C12.1, C13.1, LED1.1-VDD (VDD), LED2.1-VDD (VDD), LED3.1-VDD (VDD), LED4.1-VDD (VDD), LED5.1-VDD (VDD), LED6.1-VDD (VDD), LED7.1-VDD (VDD), LED8.1-VDD (VDD), LED9.1-VDD (VDD), LED10.1-VDD (VDD), LED11.1-VDD (VDD), LED12.1-VDD (VDD), LED13.1-VDD (VDD), U1.40 (VBUS), U1.P$40 (VBUS)
GND: C1.2, C2.2, C3.2, C4.2, C5.2, C6.2, C7.2, C8.2, C9.2, C10.2, C11.2, C12.2, C13.2, C14.2, C22.2, DISP1.1 (GND), IC1.5 (GND), J1.1, J2.1, LED1.3-GND (GND), LED2.3-GND (GND), LED3.3-GND (GND), LED4.3-GND (GND), LED5.3-GND (GND), LED6.3-GND (GND), LED7.3-GND (GND), LED8.3-GND (GND), LED9.3-GND (GND), LED10.3-GND (GND), LED11.3-GND (GND), LED12.3-GND (GND), LED13.3-GND (GND), R1.2, R2.2, R3.2, R4.2, R5.2, R6.2, R7.2, R8.2, R9.2, R10.2, R11.2, R12.2, R13.2, R14.2, R15.2, R16.2, R222.1, R333.2, U1.3 (GND), U1.8 (GND), U1.13 (GND), U1.18 (GND), U1.23 (GND), U1.28 (GND), U1.33 (GND), U1.38 (GND), U1.P$3 (GND), U1.P$8 (GND), U1.P$13 (GND), U1.P$18 (GND), U1.P$23 (GND), U1.P$28 (GND), U1.P$33 (GND), U1.P$38 (GND)
LED_DATA: LED1.4-DIN (DI), U1.21 (GP16), U1.P$21 (GP16)
MIDI_IN: IC1.4 (OUT), R777.2, U1.22 (GP17), U1.P$22 (GP17)
unnamed: LED1.2-DOUT (DO), LED2.4-DIN (DI)
unnamed: LED2.2-DOUT (DO), LED3.4-DIN (DI)
unnamed: LED4.2-DOUT (DO), LED5.4-DIN (DI)
unnamed: LED5.2-DOUT (DO), LED6.4-DIN (DI)
unnamed: LED3.2-DOUT (DO), LED4.4-DIN (DI)
unnamed: LED7.2-DOUT (DO), LED8.4-DIN (DI)
unnamed: LED8.2-DOUT (DO), LED9.4-DIN (DI)
unnamed: LED10.2-DOUT (DO), LED11.4-DIN (DI)
unnamed: LED11.2-DOUT (DO), LED12.4-DIN (DI)
unnamed: LED9.2-DOUT (DO), LED10.4-DIN (DI)
unnamed: LED6.2-DOUT (DO), LED7.4-DIN (DI)
unnamed: LED12.2-DOUT (DO), LED13.4-DIN (DI)
unnamed: D1.K (C), IC1.1 (A), R666.1
unnamed: D1.A, IC1.2 (C), J1.2
unnamed: J1.3, R666.2
unnamed: J2.2, R444.1
unnamed: J2.3, R555.1
unnamed: C21.2, R333.1, R444.2, R555.2
unnamed: C21.1, C22.1, R111.1, R222.2
PWM_AUDIO: R111.2, U1.34 (GP28), U1.P$34 (GP28)
SCL: DISP1.3 (SCL), U1.27 (GP21), U1.P$27 (GP21)
SDA: DISP1.4 (SDA), U1.26 (GP20), U1.P$26 (GP20)
SWGND: U1.42 (SWGND), U1.P$42 (SWGND)
T1: R1.1, TP1.TP, U1.1 (GP0), U1.P$1 (GP0)
T2: R2.1, TP2.TP, U1.2 (GP1), U1.P$2 (GP1)
T3: R3.1, TP3.TP, U1.4 (GP2), U1.P$4 (GP2)
T4: R4.1, TP4.TP, U1.5 (GP3), U1.P$5 (GP3)
T5: R5.1, TP5.TP, U1.6 (GP4), U1.P$6 (GP4)
T6: R6.1, TP6.TP, U1.7 (GP5), U1.P$7 (GP5)
T7: R7.1, TP7.TP, U1.9 (GP6), U1.P$9 (GP6)
T8: R8.1, TP8.TP, U1.10 (GP7), U1.P$10 (GP7)
T9: R9.1, TP9.TP, U1.11 (GP8), U1.P$11 (GP8)
T10: R10.1, TP10.TP, U1.12 (GP9), U1.P$12 (GP9)
T11: R11.1, TP11.TP, U1.14 (GP10), U1.P$14 (GP10)
T12: R12.1, TP12.TP, U1.15 (GP11), U1.P$15 (GP11)
T13: R13.1, TP13.TP, U1.16 (GP12), U1.P$16 (GP12)
T14: R14.1, TP14.TP, U1.17 (GP13), U1.P$17 (GP13)
T15: R15.1, TP15.TP, U1.19 (GP14), U1.P$19 (GP14)
T16: R16.1, TP16.TP, U1.20 (GP15), U1.P$20 (GP15)
VSYS: U1.39 (VSYS), U1.P$39 (VSYS)

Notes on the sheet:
From "3.4.1. PWM Audio" of "Hardware Design w/ RP2040"
PWM AUDIO OUT

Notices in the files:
parts and their libraries:
SparkFun-Connectors: Licensing: Creative Commons ShareAlike 4.0 International - https://creativecommons.org/licenses/by-sa/4.0
microbuilder: This work is placed in the public domain, and may be freely used for commercial and non-commercial work with the following conditions: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
